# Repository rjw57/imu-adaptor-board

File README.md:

# Spalax IMU adaptor board

This repository contains the KiCAD designs for a simple adaptor board allowing
the use of the ADIS16405 with the Spalax IMU v1 board.

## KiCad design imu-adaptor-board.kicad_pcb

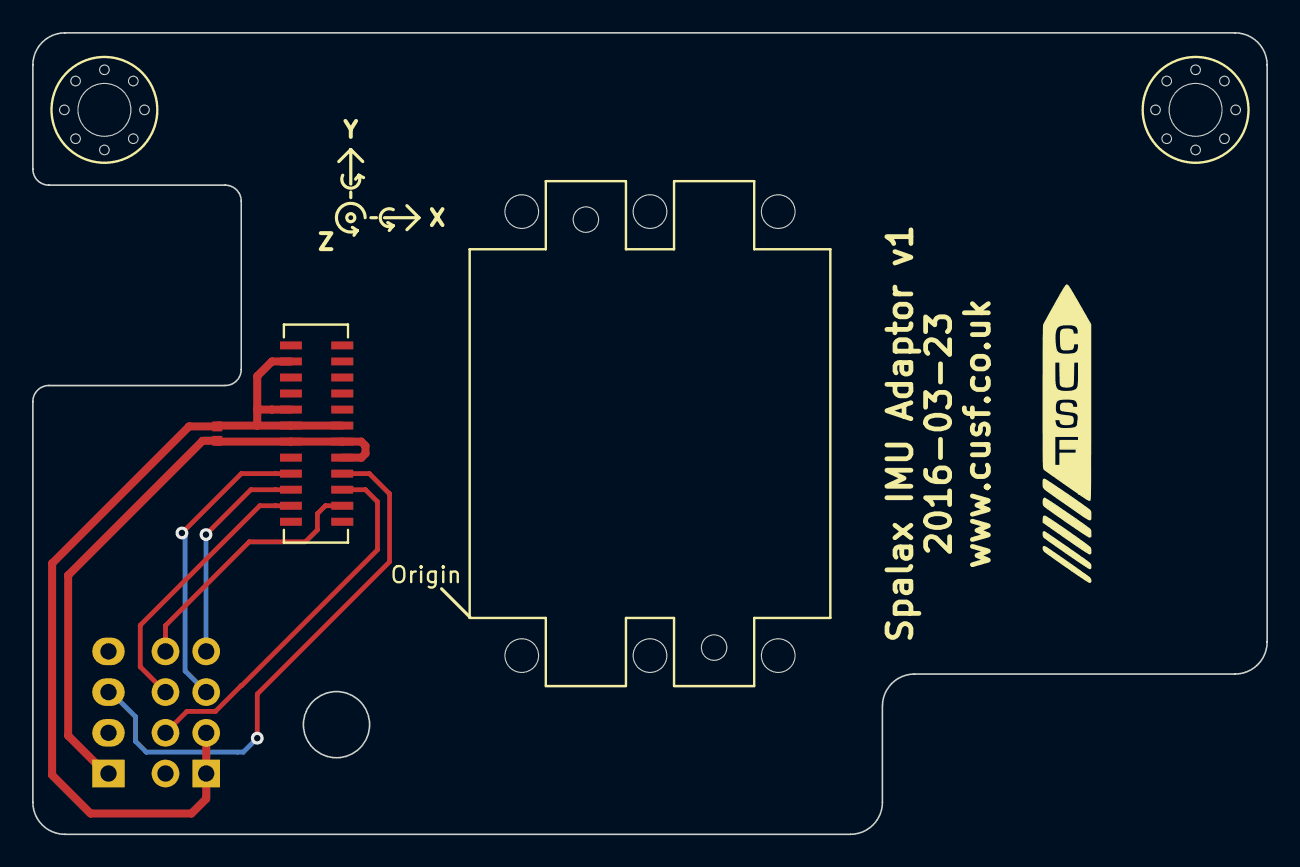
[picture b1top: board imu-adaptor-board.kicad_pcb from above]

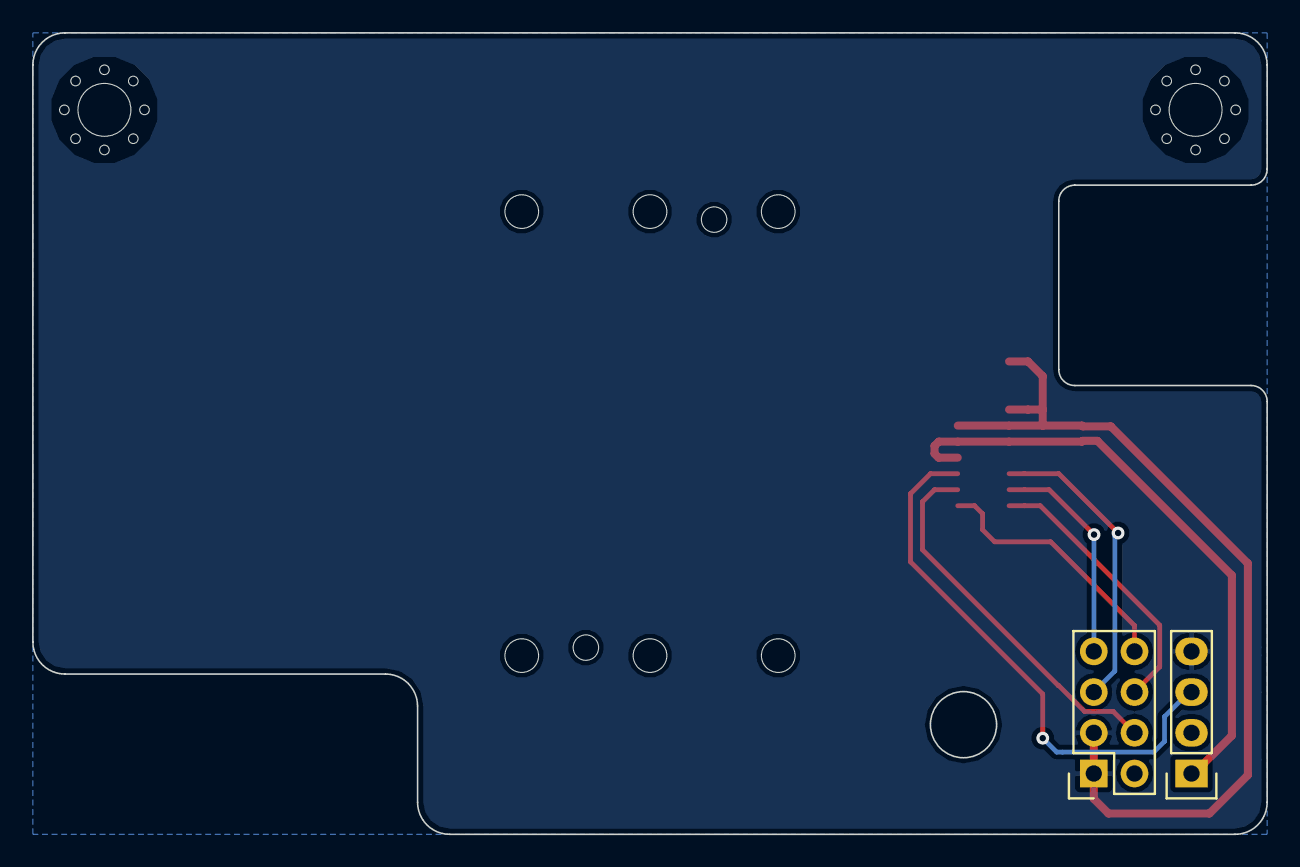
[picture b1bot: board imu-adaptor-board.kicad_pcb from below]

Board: 2 copper layers, 77.0 x 50.0 mm, 6 parts (2 on the bottom side), 8 nets.

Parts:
C1: 100n; 0402
M3_MOUNT, M3_MOUNT#2: VAL**; M3_MOUNT
P1: IMU-CAN; Socket_Strip_Straight_1x04
P2: IMU-SPI3; Socket_Strip_Straight_2x04
U1: ADIS16405BMLZ

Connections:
+5V: C1.1, P1.1, U1.10, U1.11, U1.12
/CAN1_TX: P1.3, U1.8
/DATA_RDY: P2.5, U1.7
/SPI3_MISO: P2.8, U1.4
/SPI3_MOSI: P2.7, U1.5
/SPI3_NSS: P2.4, U1.6
/SPI3_SCK: P2.6, U1.3
GND: C1.2, P1.4, P2.1, P2.3, U1.13, U1.14, U1.15, U1.21

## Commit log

2016-03-12 Add ADIS16405 origin and make board square
2016-03-12 Put CAN and SPI connector labels on back silkscreen
2016-03-12 Add gerber output
2016-03-22 add capacitor to power connector
2016-03-22 place parts so they line up with imu board
2016-03-27 change board outline to give access to ports/LEDs below
2016-03-28 new ADIS16450BMLZ footprint, all 'done'
2016-03-28 Use latest ADIS footprint
2016-03-29 make cutout for swd connector a bit bigger
2016-03-29 gerbers to manufacturing
